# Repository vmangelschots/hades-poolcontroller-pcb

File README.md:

# hades-poolcontroller-pcb
The pcb for the hades poolcontroller

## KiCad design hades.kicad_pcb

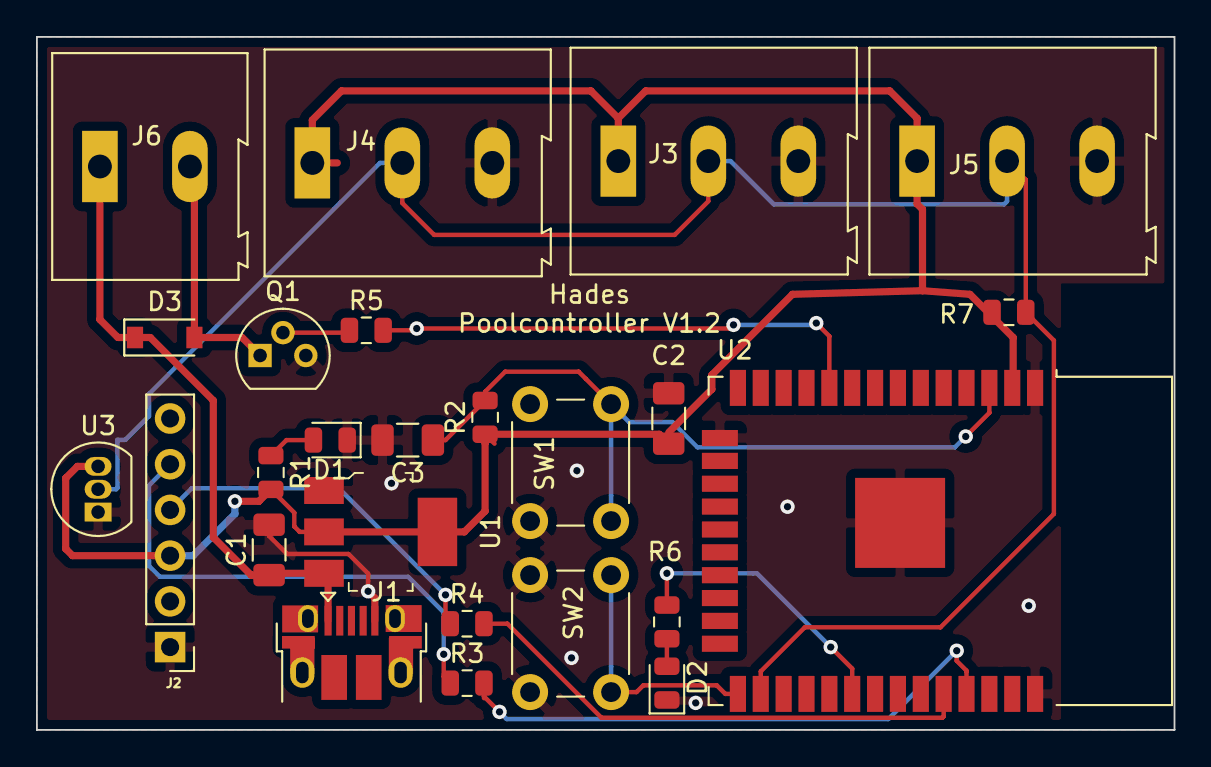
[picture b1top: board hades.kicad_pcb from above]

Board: 2 copper layers, 63.2 x 38.5 mm, 25 parts (0 on the bottom side), 16 nets.

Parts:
C1: 10µf tantalum; C_1206_3216Metric
C2: 100µf tantalum; C_1206_3216Metric
C3: 0.1µf; C_1206_3216Metric
D1: LED red; LED_0805_2012Metric
D2: LED; LED_0805_2012Metric
D3: D_Schottky; D_SOD-123
J1: USB_B_Micro; USB_Micro-B_Amphenol_10103594-0001LF_Horizontal
J2: Conn_01x06; PinHeader_1x06_P2.54mm_Vertical
J3: outgooing water temperature; TerminalBlock_Altech_AK300-3_P5.00mm
J4: incomming water temperature; TerminalBlock_Altech_AK300-3_P5.00mm
J5: Outside temperature; TerminalBlock_Altech_AK300-3_P5.00mm
J6: Relay; TerminalBlock_Altech_AK300-2_P5.00mm
Q1: 2N2222; TO-92
R1: R150; R_0805_2012Metric
R2: 10k; R_0805_2012Metric
R3, R4: 1K; R_0805_2012Metric
R5: 470; R_0805_2012Metric
R6: 56; R_0805_2012Metric
R7: 4.7k; R_0805_2012Metric
SW1: reset; SW_PUSH_6mm
SW2: mode switch; SW_PUSH_6mm
U1: LM1117MPX-3_3_NOPB; SOT-223
U2: ESP32-WROOM-32D; ESP32-WROOM-32
U3: DS18B20; TO-92_Inline

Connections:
+3V3: C2.1, J2.3, J3.1, J4.1, J5.1, R1.2, R2.1, R7.1, U1.2, U1.4, U2.2, U3.3
+5V: C1.1, D3.1, J1.1, J6.1, U1.3
/Rx: J2.4, R4.1
/Tx: J2.5, R3.1
GND: C1.2, C2.2, C3.2, D1.1, D2.1, J1.5, J2.1, J3.3, J4.3, J5.3, Q1.3, SW1.1, SW2.2, U1.1, U2.1, U2.15, U2.38, U2.39, U3.1
unnamed: C3.1, R2.2, SW1.2, U2.3
unnamed: D1.2, R1.1
unnamed: D2.2, R6.1
unnamed: D3.2, J6.2, Q1.1
unnamed: J3.2, J4.2, J5.2, R7.2, U2.26, U3.2
unnamed: Q1.2, R5.1
unnamed: R3.2, U2.35
unnamed: R4.2, U2.34
unnamed: R5.2, U2.10
unnamed: R6.2, U2.30
unnamed: SW2.1, U2.25

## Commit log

2020-05-06 commited V1
2020-05-06 fixed gitignore
2020-05-06 bugfix: on board temperature sensor connected to the other one wire devices
    bufix: The on board temperature sensor wasn't connected to the correct one wire bus
2020-05-07 fixed wrong connection to rx pin
2020-05-11 the bjt for the relay was connected to a input only pin
